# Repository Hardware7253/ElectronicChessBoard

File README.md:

# Electronic Chess Board
Welcome to the Electronic Chess Board project repository. This project combines an electronic chess board with a chess engine, offering a more tactile way to train against an AI opponent.

## Overview
The project's core objective is to deliver an interactive chess experience, allowing users to engage in matches against an AI opponent.
This AI opponent employs a minimax algorithm for strategic decision-making, with a variable search depth of 3 to 6 based on time availability. 
The chess board integrates 64 hall effect sensors to precisely detect piece positions, while the AI's moves are visually indicated using 64 LEDs.

## Code
In the [Code](/Code) directory, you'll find the firmware that powers the project. This firmware includes the chess engine responsible for AI decision-making.
The project is programmed in embedded rust, and is designed to run on the custom STM32F103C8T6 chess board.

## CAD
The [CAD](/Cad) directory contains KiCad schematics for the custom chess board PCB. Additionally, you'll find laser cutting files and 3D design files for the casing of the electronic chess board.
Manufacturing outputs for the PCB can be found in the [Manufacture](/Cad/ChessBoardKiCad/Manufacture) directory.

# Manual

## Starting the game
To begin playing, the game board will prompt you to select your team—black or white. Simply press the button while your desired team is displayed on the screen.

## Setting up the board
After starting the game, you'll be prompted to set up the chessboard. Arrange the 32 chess pieces in their starting positions, with the color that represents your team closest to you. For instance, if you are playing as the black team, ensure that the black pieces are positioned on the bottom of the board closest to you. If you need assistance during this process, you can hold down the button at any time. Doing so will illuminate LEDs on the board, indicating missing pieces or incorrectly placed ones. Once all pieces are correctly positioned, the game will automatically commence.

## Playing the game
The game follows a turn-based structure with both the user and the chess engine taking their respective turns. To make a move, simply move a chess piece and press the button to confirm that you have completed your turn. When it's the computer's turn to move, it will signal its move by blinking LEDs to indicate the destination square.

## Capturing
When capturing an opponent's piece, start by removing the captured piece from the board. Then, move your piece to its final destination and press the button to signal the end of your turn. This behavior is consistent with en passant moves, where you must first remove the captured pawn from the board before completing your move.

## Castling
To execute a castling move, move your king to its castled position without moving the rook. Press the button to indicate that you have finished your turn. After this, you may move your rook to the opposite side of the king to complete the castling maneuver.

## Errors
Errors are most likely to occur when an illegal move is made. The board's LEDs will illuminate to highlight the pieces that need adjustment to rectify the error. Additionally, the LCD screen will prompt you to revert the piece positions.

Errors may also happen when pieces are moved during the chess engine's turn. In such cases, you may notice multiple LEDs being lit up, some indicating the engine's move and others indicating pieces in the wrong position. This typically occurs when one or more pieces are slightly off-center on their squares. To resolve this issue, simply adjust the misaligned pieces inward slightly to correct the error.

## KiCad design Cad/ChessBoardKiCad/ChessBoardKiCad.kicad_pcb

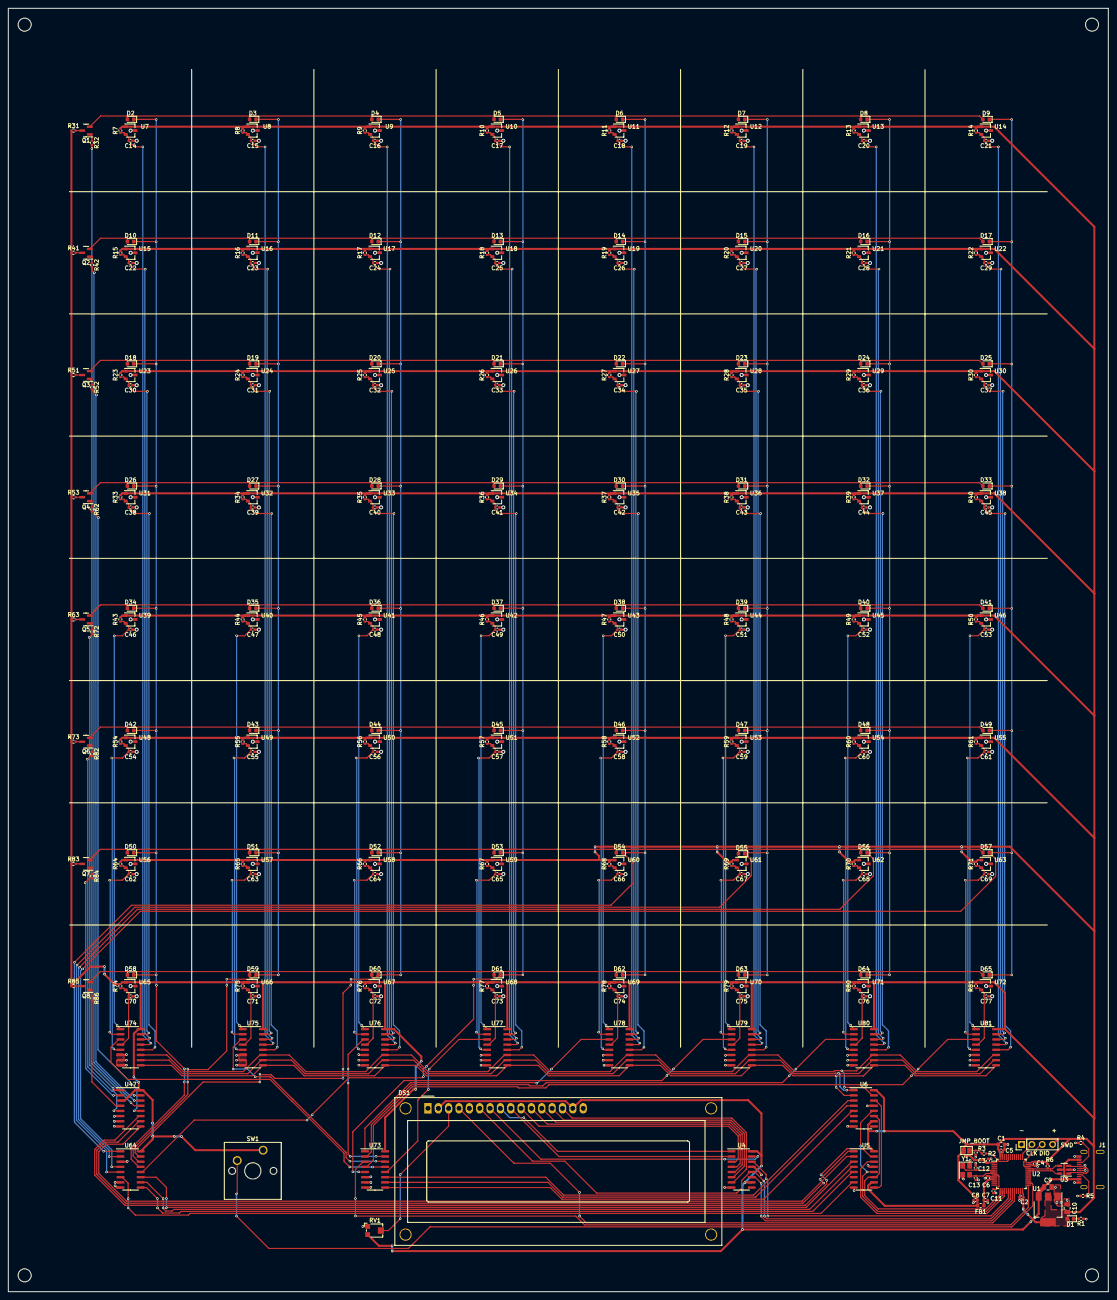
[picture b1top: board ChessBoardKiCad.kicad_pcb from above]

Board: 2 copper layers, 270.0 x 315.0 mm, 329 parts (0 on the bottom side), 162 nets.

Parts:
C1: 10u; C_0603_1608Metric
C2, C3, C4, C5, C11, C14, C15, C16, C17, C18, C19, C20, C21, C22, C23, C24, C25, C26, C27, C28, C29, C30, C31, C32, C33, C34, C35, C36, C37, C38, C39, C40, C41, C42, C43, C44, C45, C46, C47, C48, C49, C50, C51, C52, C53, C54, C55, C56, C57, C58, C59, C60, C61, C62, C63, C64, C65, C66, C67, C68, C69, C70, C71, C72, C73, C74, C75, C76, C77: 100n; C_0402_1005Metric
C6: 10n; C_0402_1005Metric
C7, C8: 1u; C_0402_1005Metric
C9, C10: 22u; C_0805_2012Metric
C12, C13: 14p; C_0402_1005Metric
D1, D2, D3, D4, D5, D6, D7, D8, D9, D10, D11, D12, D13, D14, D15, D16, D17, D18, D19, D20, D21, D22, D23, D24, D25, D26, D27, D28, D29, D30, D31, D32, D33, D34, D35, D36, D37, D38, D39, D40, D41, D42, D43, D44, D45, D46, D47, D48, D49, D50, D51, D52, D53, D54, D55, D56, D57, D58, D59, D60, D61, D62, D63, D64, D65: RED; LED_0603_1608Metric
DS1: WC1602A
FB1: 120R; L_0603_1608Metric
H1, H2, H3, H4: MountingHole; MountingHole_3.2mm_M3
J1: USB_C_Receptacle; USB-310D-B-SU
J2: Conn_01x04_Pin; PinHeader_1x04_P2.54mm_Vertical
JP1: SolderJumper_2_Open; SolderJumper-2_P1.3mm_Open_Pad1.0x1.5mm
Q1, Q2, Q3, Q4, Q5, Q6, Q7, Q8: S9013; SOT-23
R1, R6, R31, R41, R51, R53, R63, R73, R83, R85: 1k5; R_0402_1005Metric
R2, R3, R32, R42, R52, R62, R72, R82, R84, R86: 10k; R_0402_1005Metric
R4, R5: 5k1; R_0402_1005Metric
R7, R8, R9, R10, R11, R12, R13, R14, R15, R16, R17, R18, R19, R20, R21, R22, R23, R24, R25, R26, R27, R28, R29, R30, R33, R34, R35, R36, R37, R38, R39, R40, R43, R44, R45, R46, R47, R48, R49, R50, R54, R55, R56, R57, R58, R59, R60, R61, R64, R65, R66, R67, R68, R69, R70, R71, R74, R75, R76, R77, R78, R79, R80, R81: 2k7; R_0402_1005Metric
RV1: 10k; Potentiometer_Bourns_TC33X_Vertical
SW1: SW_SPST; SW_Cherry_MX_1.00u_PCB
U1: AMS1117-3.3; SOT-223-3_TabPin2
U2: STM32F103C8T6; LQFP-48_7x7mm_P0.5mm
U3: USBLC6-2SC6; SOT-23-6
U4, U5, U6: 74HC595; SOIC-16_3.9x9.9mm_P1.27mm
U7, U8, U9, U10, U11, U12, U13, U14, U15, U16, U17, U18, U19, U20, U21, U22, U23, U24, U25, U26, U27, U28, U29, U30, U31, U32, U33, U34, U35, U36, U37, U38, U39, U40, U41, U42, U43, U44, U45, U46, U48, U49, U50, U51, U52, U53, U54, U55, U56, U57, U58, U59, U60, U61, U62, U63, U65, U66, U67, U68, U69, U70, U71, U72: UHE4913G-AE3-R; SOT-23W
U47, U64, U73, U74, U75, U76, U77, U78, U79, U80, U81: CD4051BM; SOIC-16_3.9x9.9mm_P1.27mm
Y1: 8Mhz; Crystal_SMD_3225-4Pin_3.2x2.5mm

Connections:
+3.3V: C1.1, C2.1, C3.1, C4.1, C5.1, C8.1, C10.1, D1.2 (A), FB1.2, J2.4, JP1.1 (A), R6.2, R7.1, R8.1, R9.1, R10.1, R11.1, R12.1, R13.1, R14.1, R15.1, R16.1, R17.1, R18.1, R19.1, R20.1, R21.1, R22.1, R23.1, R24.1, R25.1, R26.1, R27.1, R28.1, R29.1, R30.1, R31.1, R33.1, R34.1, R35.1, R36.1, R37.1, R38.1, R39.1, R40.1, R41.1, R43.1, R44.1, R45.1, R46.1, R47.1, R48.1, R49.1, R50.1, R51.1, R53.1, R54.1, R55.1, R56.1, R57.1, R58.1, R59.1, R60.1, R61.1, R63.1, R64.1, R65.1, R66.1, R67.1, R68.1, R69.1, R70.1, R71.1, R73.1, R74.1, R75.1, R76.1, R77.1, R78.1, R79.1, R80.1, R81.1, R83.1, R85.1, SW1.1 (A), U1.2 (VO), U2.1 (VBAT), U2.24 (VDD), U2.36 (VDD), U2.48 (VDD), U5.10 (~SRCLR), U5.16 (VCC), U6.10 (~SRCLR), U6.16 (VCC), U7.1 (VCC), U8.1 (VCC), U9.1 (VCC), U10.1 (VCC), U11.1 (VCC), U12.1 (VCC), U13.1 (VCC), U14.1 (VCC), U15.1 (VCC), U16.1 (VCC), U17.1 (VCC), U18.1 (VCC), U19.1 (VCC), U20.1 (VCC), U21.1 (VCC), U22.1 (VCC), U23.1 (VCC), U24.1 (VCC), U25.1 (VCC), U26.1 (VCC), U27.1 (VCC), U28.1 (VCC), U29.1 (VCC), U30.1 (VCC), U31.1 (VCC), U32.1 (VCC), U33.1 (VCC), U34.1 (VCC), U35.1 (VCC), U36.1 (VCC), U37.1 (VCC), U38.1 (VCC), U39.1 (VCC), U40.1 (VCC), U41.1 (VCC), U42.1 (VCC), U43.1 (VCC), U44.1 (VCC), U45.1 (VCC), U46.1 (VCC), U47.3 (X), U47.16 (VDD), U48.1 (VCC), U49.1 (VCC), U50.1 (VCC), U51.1 (VCC), U52.1 (VCC), U53.1 (VCC), U54.1 (VCC), U55.1 (VCC), U56.1 (VCC), U57.1 (VCC), U58.1 (VCC), U59.1 (VCC), U60.1 (VCC), U61.1 (VCC), U62.1 (VCC), U63.1 (VCC), U64.16 (VDD), U65.1 (VCC), U66.1 (VCC), U67.1 (VCC), U68.1 (VCC), U69.1 (VCC), U70.1 (VCC), U71.1 (VCC), U72.1 (VCC), U73.16 (VDD), U74.16 (VDD), U75.16 (VDD), U76.16 (VDD), U77.16 (VDD), U78.16 (VDD), U79.16 (VDD), U80.16 (VDD), U81.16 (VDD)
+3.3VA: C6.1, C7.1, FB1.1, U2.9 (VDDA)
/BOOT0: R2.1, U2.44 (BOOT0)
/CONT_1: DS1.3 (VO), RV1.2
/GRID_REGS_SER_LINK: U5.9 (QH'), U6.14 (SER)
/HSE_IN: C12.1, U2.5 (PD0), Y1.1
/HSE_OUT: C13.1, U2.6 (PD1), Y1.3
/JMP_BOOT0: JP1.2 (B), R2.2, R3.2
/LCD1_D0: DS1.7 (D0), U4.15 (QA)
/LCD1_D1: DS1.8 (D1), U4.1 (QB)
/LCD1_D2: DS1.9 (D2), U4.2 (QC)
/LCD1_D3: DS1.10 (D3), U4.3 (QD)
/LCD1_D4: DS1.11 (D4), U4.4 (QE)
/LCD1_D5: DS1.12 (D5), U4.5 (QF)
/LCD1_D6: DS1.13 (D6), U4.6 (QG)
/LCD1_D7: DS1.14 (D7), U4.7 (QH)
/NRST: C11.1, U2.7 (NRST)
/PWR_LED_K: D1.1 (K), R1.2
/R0TB: Q1.1 (B), R32.1
/R0TC: Q1.3 (C), R31.2
/R0TE: D2.2 (A), D3.2 (A), D4.2 (A), D5.2 (A), D6.2 (A), D7.2 (A), D8.2 (A), D9.2 (A), Q1.2 (E)
/R1TB: Q2.1 (B), R42.1
/R1TC: Q2.3 (C), R41.2
/R1TE: D10.2 (A), D11.2 (A), D12.2 (A), D13.2 (A), D14.2 (A), D15.2 (A), D16.2 (A), D17.2 (A), Q2.2 (E)
/R2TB: Q3.1 (B), R52.1
/R2TC: Q3.3 (C), R51.2
/R2TE: D18.2 (A), D19.2 (A), D20.2 (A), D21.2 (A), D22.2 (A), D23.2 (A), D24.2 (A), D25.2 (A), Q3.2 (E)
/R3TB: Q4.1 (B), R62.1
/R3TC: Q4.3 (C), R53.2
/R3TE: D26.2 (A), D27.2 (A), D28.2 (A), D29.2 (A), D30.2 (A), D31.2 (A), D32.2 (A), D33.2 (A), Q4.2 (E)
/R4TB: Q5.1 (B), R72.1
/R4TC: Q5.3 (C), R63.2
/R4TE: D34.2 (A), D35.2 (A), D36.2 (A), D37.2 (A), D38.2 (A), D39.2 (A), D40.2 (A), D41.2 (A), Q5.2 (E)
/R5TB: Q6.1 (B), R82.1
/R5TC: Q6.3 (C), R73.2
/R5TE: D42.2 (A), D43.2 (A), D44.2 (A), D45.2 (A), D46.2 (A), D47.2 (A), D48.2 (A), D49.2 (A), Q6.2 (E)
/R6TB: Q7.1 (B), R84.1
/R6TC: Q7.3 (C), R83.2
/R6TE: D50.2 (A), D51.2 (A), D52.2 (A), D53.2 (A), D54.2 (A), D55.2 (A), D56.2 (A), D57.2 (A), Q7.2 (E)
/R7TB: Q8.1 (B), R86.1
/R7TC: Q8.3 (C), R85.2
/R7TE: D58.2 (A), D59.2 (A), D60.2 (A), D61.2 (A), D62.2 (A), D63.2 (A), D64.2 (A), D65.2 (A), Q8.2 (E)
/SWCLK: J2.2, U2.37 (PA14)
/SWDIO: J2.3, U2.34 (PA13)
/USB_CC1: J1.A5 (CC1), R5.2
/USB_CC2: J1.B5 (CC2), R4.2
BUTTON: SW1.2 (B), U2.26 (PB13)
DISABLE_LEDS: U5.7 (QH), U64.6 (Inh)
GND: C1.2, C2.2, C3.2, C4.2, C5.2, C6.2, C7.2, C8.2, C9.2, C10.2, C11.2, C12.2, C13.2, C14.2, C15.2, C16.2, C17.2, C18.2, C19.2, C20.2, C21.2, C22.2, C23.2, C24.2, C25.2, C26.2, C27.2, C28.2, C29.2, C30.2, C31.2, C32.2, C33.2, C34.2, C35.2, C36.2, C37.2, C38.2, C39.2, C40.2, C41.2, C42.2, C43.2, C44.2, C45.2, C46.2, C47.2, C48.2, C49.2, C50.2, C51.2, C52.2, C53.2, C54.2, C55.2, C56.2, C57.2, C58.2, C59.2, C60.2, C61.2, C62.2, C63.2, C64.2, C65.2, C66.2, C67.2, C68.2, C69.2, C70.2, C71.2, C72.2, C73.2, C74.2, C75.2, C76.2, C77.2, DS1.1 (VSS), DS1.5 (R/W), DS1.16 (LED(-)), J1.A1 (GND), J1.A12 (GND), J1.B1 (GND), J1.B12 (GND), J2.1, R1.1, R3.1, R4.1, R5.1, RV1.1, U1.1 (GND), U2.8 (VSSA), U2.23 (VSS), U2.35 (VSS), U2.47 (VSS), U3.2 (GND), U4.8 (GND), U4.13 (~OE), U5.8 (GND), U5.13 (~OE), U6.8 (GND), U6.13 (~OE), U7.3 (GND), U8.3 (GND), U9.3 (GND), U10.3 (GND), U11.3 (GND), U12.3 (GND), U13.3 (GND), U14.3 (GND), U15.3 (GND), U16.3 (GND), U17.3 (GND), U18.3 (GND), U19.3 (GND), U20.3 (GND), U21.3 (GND), U22.3 (GND), U23.3 (GND), U24.3 (GND), U25.3 (GND), U26.3 (GND), U27.3 (GND), U28.3 (GND), U29.3 (GND), U30.3 (GND), U31.3 (GND), U32.3 (GND), U33.3 (GND), U34.3 (GND), U35.3 (GND), U36.3 (GND), U37.3 (GND), U38.3 (GND), U39.3 (GND), U40.3 (GND), U41.3 (GND), U42.3 (GND), U43.3 (GND), U44.3 (GND), U45.3 (GND), U46.3 (GND), U47.6 (Inh), U47.7 (VEE), U47.8 (VSS), U48.3 (GND), U49.3 (GND), U50.3 (GND), U51.3 (GND), U52.3 (GND), U53.3 (GND), U54.3 (GND), U55.3 (GND), U56.3 (GND), U57.3 (GND), U58.3 (GND), U59.3 (GND), U60.3 (GND), U61.3 (GND), U62.3 (GND), U63.3 (GND), U64.3 (X), U64.7 (VEE), U64.8 (VSS), U65.3 (GND), U66.3 (GND), U67.3 (GND), U68.3 (GND), U69.3 (GND), U70.3 (GND), U71.3 (GND), U72.3 (GND), U73.6 (Inh), U73.7 (VEE), U73.8 (VSS), U74.6 (Inh), U74.7 (VEE), U74.8 (VSS), U75.6 (Inh), U75.7 (VEE), U75.8 (VSS), U76.6 (Inh), U76.7 (VEE), U76.8 (VSS), U77.6 (Inh), U77.7 (VEE), U77.8 (VSS), U78.6 (Inh), U78.7 (VEE), U78.8 (VSS), U79.6 (Inh), U79.7 (VEE), U79.8 (VSS), U80.6 (Inh), U80.7 (VEE), U80.8 (VSS), U81.6 (Inh), U81.7 (VEE), U81.8 (VSS), Y1.2, Y1.4
GRID_LATCH: U2.14 (PA4), U5.12 (RCLK), U6.12 (RCLK)
GRID_SER_CLK: U2.13 (PA3), U5.11 (SRCLK), U6.11 (SRCLK)
GRID_SER_DATA: U2.15 (PA5), U5.14 (SER)
HALL_C0: U73.13 (X0), U74.3 (X)
HALL_C0R0: C14.1, R7.2, U7.2 (VOUT), U74.13 (X0)
HALL_C0R1: C22.1, R15.2, U15.2 (VOUT), U74.14 (X1)
HALL_C0R2: C30.1, R23.2, U23.2 (VOUT), U74.15 (X2)
HALL_C0R3: C38.1, R33.2, U31.2 (VOUT), U74.12 (X3)
HALL_C0R4: C46.1, R43.2, U39.2 (VOUT), U74.1 (X4)
HALL_C0R5: C54.1, R54.2, U48.2 (VOUT), U74.5 (X5)
HALL_C0R6: C62.1, R64.2, U56.2 (VOUT), U74.2 (X6)
HALL_C0R7: C70.1, R74.2, U65.2 (VOUT), U74.4 (X7)
HALL_C1: U73.14 (X1), U75.3 (X)
HALL_C1R0: C15.1, R8.2, U8.2 (VOUT), U75.13 (X0)
HALL_C1R1: C23.1, R16.2, U16.2 (VOUT), U75.14 (X1)
HALL_C1R2: C31.1, R24.2, U24.2 (VOUT), U75.15 (X2)
HALL_C1R3: C39.1, R34.2, U32.2 (VOUT), U75.12 (X3)
HALL_C1R4: C47.1, R44.2, U40.2 (VOUT), U75.1 (X4)
HALL_C1R5: C55.1, R55.2, U49.2 (VOUT), U75.5 (X5)
HALL_C1R6: C63.1, R65.2, U57.2 (VOUT), U75.2 (X6)
HALL_C1R7: C71.1, R75.2, U66.2 (VOUT), U75.4 (X7)
HALL_C2: U73.15 (X2), U76.3 (X)
HALL_C2R0: C16.1, R9.2, U9.2 (VOUT), U76.13 (X0)
HALL_C2R1: C24.1, R17.2, U17.2 (VOUT), U76.14 (X1)
HALL_C2R2: C32.1, R25.2, U25.2 (VOUT), U76.15 (X2)
HALL_C2R3: C40.1, R35.2, U33.2 (VOUT), U76.12 (X3)
HALL_C2R4: C48.1, R45.2, U41.2 (VOUT), U76.1 (X4)
HALL_C2R5: C56.1, R56.2, U50.2 (VOUT), U76.5 (X5)
HALL_C2R6: C64.1, R66.2, U58.2 (VOUT), U76.2 (X6)
HALL_C2R7: C72.1, R76.2, U67.2 (VOUT), U76.4 (X7)
HALL_C3: U73.12 (X3), U77.3 (X)
HALL_C3R0: C17.1, R10.2, U10.2 (VOUT), U77.13 (X0)
HALL_C3R1: C25.1, R18.2, U18.2 (VOUT), U77.14 (X1)
HALL_C3R2: C33.1, R26.2, U26.2 (VOUT), U77.15 (X2)
HALL_C3R3: C41.1, R36.2, U34.2 (VOUT), U77.12 (X3)
HALL_C3R4: C49.1, R46.2, U42.2 (VOUT), U77.1 (X4)
HALL_C3R5: C57.1, R57.2, U51.2 (VOUT), U77.5 (X5)
HALL_C3R6: C65.1, R67.2, U59.2 (VOUT), U77.2 (X6)
HALL_C3R7: C73.1, R77.2, U68.2 (VOUT), U77.4 (X7)
HALL_C4: U73.1 (X4), U78.3 (X)
HALL_C4R0: C18.1, R11.2, U11.2 (VOUT), U78.13 (X0)
HALL_C4R1: C26.1, R19.2, U19.2 (VOUT), U78.14 (X1)
HALL_C4R2: C34.1, R27.2, U27.2 (VOUT), U78.15 (X2)
HALL_C4R3: C42.1, R37.2, U35.2 (VOUT), U78.12 (X3)
HALL_C4R4: C50.1, R47.2, U43.2 (VOUT), U78.1 (X4)
HALL_C4R5: C58.1, R58.2, U52.2 (VOUT), U78.5 (X5)
HALL_C4R6: C66.1, R68.2, U60.2 (VOUT), U78.2 (X6)
HALL_C4R7: C74.1, R78.2, U69.2 (VOUT), U78.4 (X7)
HALL_C5: U73.5 (X5), U79.3 (X)
HALL_C5R0: C19.1, R12.2, U12.2 (VOUT), U79.13 (X0)
HALL_C5R1: C27.1, R20.2, U20.2 (VOUT), U79.14 (X1)
HALL_C5R2: C35.1, R28.2, U28.2 (VOUT), U79.15 (X2)
HALL_C5R3: C43.1, R38.2, U36.2 (VOUT), U79.12 (X3)
HALL_C5R4: C51.1, R48.2, U44.2 (VOUT), U79.1 (X4)
HALL_C5R5: C59.1, R59.2, U53.2 (VOUT), U79.5 (X5)
HALL_C5R6: C67.1, R69.2, U61.2 (VOUT), U79.2 (X6)
HALL_C5R7: C75.1, R79.2, U70.2 (VOUT), U79.4 (X7)
HALL_C6: U73.2 (X6), U80.3 (X)
HALL_C6R0: C20.1, R13.2, U13.2 (VOUT), U80.13 (X0)
HALL_C6R1: C28.1, R21.2, U21.2 (VOUT), U80.14 (X1)
HALL_C6R2: C36.1, R29.2, U29.2 (VOUT), U80.15 (X2)
HALL_C6R3: C44.1, R39.2, U37.2 (VOUT), U80.12 (X3)
HALL_C6R4: C52.1, R49.2, U45.2 (VOUT), U80.1 (X4)
HALL_C6R5: C60.1, R60.2, U54.2 (VOUT), U80.5 (X5)
HALL_C6R6: C68.1, R70.2, U62.2 (VOUT), U80.2 (X6)
HALL_C6R7: C76.1, R80.2, U71.2 (VOUT), U80.4 (X7)
HALL_C7: U73.4 (X7), U81.3 (X)
HALL_C7R0: C21.1, R14.2, U14.2 (VOUT), U81.13 (X0)
HALL_C7R1: C29.1, R22.2, U22.2 (VOUT), U81.14 (X1)
HALL_C7R2: C37.1, R30.2, U30.2 (VOUT), U81.15 (X2)
HALL_C7R3: C45.1, R40.2, U38.2 (VOUT), U81.12 (X3)
HALL_C7R4: C53.1, R50.2, U46.2 (VOUT), U81.1 (X4)
HALL_C7R5: C61.1, R61.2, U55.2 (VOUT), U81.5 (X5)
HALL_C7R6: C69.1, R71.2, U63.2 (VOUT), U81.2 (X6)
HALL_C7R7: C77.1, R81.2, U72.2 (VOUT), U81.4 (X7)
HALL_COL_A: U6.3 (QD), U73.11 (A)
HALL_COL_B: U6.4 (QE), U73.10 (B)
HALL_COL_C: U6.5 (QF), U73.9 (C)
HALL_ROW_A: U6.15 (QA), U74.11 (A), U75.11 (A), U76.11 (A), U77.11 (A), U78.11 (A), U79.11 (A), U80.11 (A), U81.11 (A)
HALL_ROW_B: U6.1 (QB), U74.10 (B), U75.10 (B), U76.10 (B), U77.10 (B), U78.10 (B), U79.10 (B), U80.10 (B), U81.10 (B)
HALL_ROW_C: U6.2 (QC), U74.9 (C), U75.9 (C), U76.9 (C), U77.9 (C), U78.9 (C), U79.9 (C), U80.9 (C), U81.9 (C)
LCD_LATCH: DS1.6 (E), U2.18 (PB0), U4.12 (RCLK)
LCD_RS: DS1.4 (RS), U2.20 (PB2)
LCD_SER_CLK: U2.19 (PB1), U4.11 (SRCLK)
LCD_SER_DATA: U2.17 (PA7), U4.14 (SER)
LED_C0: D2.1 (K), D10.1 (K), D18.1 (K), D26.1 (K), D34.1 (K), D42.1 (K), D50.1 (K), D58.1 (K), U64.13 (X0)
LED_C1: D3.1 (K), D11.1 (K), D19.1 (K), D27.1 (K), D35.1 (K), D43.1 (K), D51.1 (K), D59.1 (K), U64.14 (X1)
LED_C2: D4.1 (K), D12.1 (K), D20.1 (K), D28.1 (K), D36.1 (K), D44.1 (K), D52.1 (K), D60.1 (K), U64.15 (X2)
LED_C3: D5.1 (K), D13.1 (K), D21.1 (K), D29.1 (K), D37.1 (K), D45.1 (K), D53.1 (K), D61.1 (K), U64.12 (X3)
LED_C4: D6.1 (K), D14.1 (K), D22.1 (K), D30.1 (K), D38.1 (K), D46.1 (K), D54.1 (K), D62.1 (K), U64.1 (X4)
LED_C5: D7.1 (K), D15.1 (K), D23.1 (K), D31.1 (K), D39.1 (K), D47.1 (K), D55.1 (K), D63.1 (K), U64.5 (X5)
LED_C6: D8.1 (K), D16.1 (K), D24.1 (K), D32.1 (K), D40.1 (K), D48.1 (K), D56.1 (K), D64.1 (K), U64.2 (X6)
LED_C7: D9.1 (K), D17.1 (K), D25.1 (K), D33.1 (K), D41.1 (K), D49.1 (K), D57.1 (K), D65.1 (K), U64.4 (X7)
LED_COL_A: U5.3 (QD), U64.11 (A)
LED_COL_B: U5.4 (QE), U64.10 (B)
LED_COL_C: U5.5 (QF), U64.9 (C)
LED_R0: R32.2, U47.13 (X0)
LED_R1: R42.2, U47.14 (X1)
LED_R2: R52.2, U47.15 (X2)
LED_R3: R62.2, U47.12 (X3)
LED_R4: R72.2, U47.1 (X4)
LED_R5: R82.2, U47.5 (X5)
LED_R6: R84.2, U47.2 (X6)
LED_R7: R86.2, U47.4 (X7)
LED_ROW_A: U5.15 (QA), U47.11 (A)
LED_ROW_B: U5.1 (QB), U47.10 (B)
LED_ROW_C: U5.2 (QC), U47.9 (C)
SELECTED_HALL: U2.25 (PB12), U73.3 (X)
USB_CON_D+: J1.A6 (D+), J1.B6 (D+), U3.3 (I/O2)
USB_CON_D-: J1.A7 (D-), J1.B7 (D-), U3.1 (I/O1)
USB_D+: R6.1, U2.33 (PA12), U3.4 (I/O2)
USB_D-: U2.32 (PA11), U3.6 (I/O1)
VBUS: C9.1, DS1.2 (VDD), DS1.15 (LED(+)), J1.A4 (VBUS), J1.A9 (VBUS), J1.B4 (VBUS), J1.B9 (VBUS), RV1.3, U1.3 (VI), U3.5 (VBUS), U4.10 (~SRCLR), U4.16 (VCC)

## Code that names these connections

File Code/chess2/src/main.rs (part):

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
    // Initialise hall and led grid shift register
    let mut grid_sr = embedded::ShiftRegister {
        clock: gpioa.pa3.into_push_pull_output(&mut gpioa.crl).downgrade(),
        data: gpioa.pa5.into_push_pull_output(&mut gpioa.crl).downgrade(),
        latch: gpioa.pa4.into_push_pull_output(&mut gpioa.crl).downgrade(),
        bits: 16,
    };
    grid_sr.init(&mut delay);
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    // Initialise character lcd
    let mut lcd = embedded::character_lcd::Lcd {
        shift_register: embedded::ShiftRegister {
            clock: gpiob.pb1.into_push_pull_output(&mut gpiob.crl).downgrade(),
            data: gpioa.pa7.into_push_pull_output(&mut gpioa.crl).downgrade(),
            latch: gpiob.pb0.into_push_pull_output(&mut gpiob.crl).downgrade(),
            bits: 8,
        },
        register_select: gpiob.pb2.into_push_pull_output(&mut gpiob.crl).downgrade(),
    };
    lcd.init(&mut delay);

    let hall_sensor = gpiob.pb12.into_floating_input(&mut gpiob.crh).downgrade(); // Pin to read value of the selected hall sensor

    let mut button = embedded::button::Button {
        pin: gpiob.pb13.into_pull_down_input(&mut gpiob.crh).downgrade(),
        press_raw: false,
        press_start_cycle: None,
        long_press_cycles: embedded::ms_to_cycles(650, clock_mhz as u64), // Button needs to be held for atleast 650ms for a long press
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
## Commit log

2023-03-17 Full utilization of fen
2023-03-17 Started move generation
    Added function to check if a move on a bitboard still fits within
    cartesian bitboard. Also removed constants for piece_ids.
2023-03-18 Added basic move generation
    Made a function which returns a bitboard, where a bit switched to 1
    indicates that the given piece can move there. No advanced functionality
    such as en passant, double move, or castling is implemented yet.
2023-03-19 Added special pawn moves
    Added en passant, double moves, and special capture moves.
2023-03-21 Added a castling function
2023-03-22 Bugfixed castle function
2023-03-24 Added function to generate enemy attacks
    Function generates enemy attacks, and stores coordinates of pieces
    putting the king in check.
2023-03-25 Added function to check for mate
    Returns true/false if a king is in mate. Can be used to check for
    checkmate and stalemate.
2023-03-26 is_mate bufix
    Fixed scenario where a checkmate was not registered because a pawn had a
    valid move.
2023-03-29 Added new_turn function
    Function returns a new board if the move is valid including updated bitboards, points, etc.
2023-03-30 new_turn now returns an error enum
    Error enum has more detailed information about why the move failed.
    Additionally added check to see if moving the piece results in checkmate
    or stalemate so the game can be ended.
2023-03-31 Added a move orderer
    To be used with best_move minimax function
2023-03-31 Added gen_best_move function
    Finds the best move on the board with a given depth. Uses minimax
    algorithms. Also made bugfixes regarding kings being able to move into
    check.
2023-03-31 Added alpha beta pruning
    Branches will now be pruned if they aren't necassary to search. Fixed
    bug in is_mate. Fixed bug in new_turn where en_passant capture would not
    give any value.
2023-03-31 More is_mate bugfixes
    Fixed is_mate not accounting for moves which can block the checking
    pieces path.
2023-04-04 Added fen_encode function
    Made a debugging function to encode the engines board representation into a fen
    string.
2023-04-05 midway through is_mate bugfix
2023-04-06 is_mate bugfix
    Fixed is_mate not accounting for moves of pieces not putting the king in
    check. This could be a problem if a friendly piece tries to capture an
    enemy piece putting the king in check, but exposes check from another
    piece.
2023-04-08 Game is playable against ai.
    Running the program now allows a player to verse the minimax algorithm.
    Bugfixed black pawns moving improperly aswell.
2023-04-09 Added pawn piece promotion
    Basic pawn promotion where they always promote to queens. Additionally
    made bugfix to castle where a king could still castle after it had moved.
    Also fixed moves bitboard not being correct for the king bits when queen and kingside could be
    castled to.
2023-04-13 Fixed bug in new_turn
    Fixed bug where team bitboards were not being updated when a capture
    happened. This caused false checkmates during a game.
2023-04-14 Bugfixed castle and is mate
    Removed unnecasary break from is mate to stop it returning early when
    checking if the king is able to move to any squares. Added condition to
    castle function that checks the rook at rook_bit actaully exists on the
    board.
2023-04-17 Overhauled is_mate function
    Rewrote the majority of is_mate to reduce bugs, and to simplify it.
    Simplifaction will allow easier bug fixing in the future.
2023-04-21 is_mate bugfix
    Fixed bug with is_mate where a square that a pawn was attacking could
    block a checking piece. The pawn couldn't actually move to this square,
    so a fix was implemented that checks if the pawn can actually move to
    the square where it is trying to block mate.
    Additionally tried to add heatmaps for piece advantageous squares. After
    implementing a new way to sort the moves in order_moves I tested it, and
2023-04-21 Opening heatmaps implemented
    The ai now conisders values from the opening heatmaps when making a
    move. Additionally fixed castling reseting turns_since_capture in
    new_turn.
2023-04-22 Added zobrist hashing
    Made relevant functions for zobrist hashing. They work but the feature
    hasn't yet been implemented into the best_move algorithm.
2023-04-24 Implemented transposition table
    Transpositions are now used in the best_move function to save time
    reevaluating positions. Additionally made the half move clock work
    properly.
2023-04-28 is_mate bugfix
    Added additional condition when returning false, king must not be in
    check after a move that blocks the initial check. Additionally made old
    moves in transposition table delete themselves. And gave a value for
    pawn promotion to queen. This encourages the algorithm to promote.
2023-05-01 Fixed typo affecting minimax algorithm
    Typo in the alpha beta pruning caused function to never return minimum
    values. The typo has been fixed. Additionally order_move now used a
    change in the heatmap value from the initial to the final square. So a
    piece is encouraged to hold an advantageous square.
2023-05-05 Added zobrist hashing to a test
    Speed of the best_move function can be more accurately tested
2023-05-07 Added iterative deepening
    Best moves from lower search depths are search first. This currently
    results in a longer search time overall. I think there is a bug in the
    pruning which I will have to fix.
2023-05-09 Changed alpha beta implementation
    Currently broken
2023-05-10 fixed alpha beta pruning
2023-05-12 Added timeout best_move function
    When the master branch of best_move has been running more than the
    maximum ammount of milliseconds it is aloud to run for it returns the pv
    move from a lower search depth.
2023-05-13 Removed vec and hashmaps
    Removed the transposition table which relies on hashmaps. And changed
    from a vec to an array for sorted moves at a detrement to performance.
    These changes were made to remove core functions reliance on std to make
    running on an embedded system easier.
2023-05-16 first embedded commit
    Removed unnecary debugging and testing code, and completely eliminated
    the std library. Project is now setup to run the chess engine on an
    stm32f103c8t6.
2023-05-28 Added KiCad project
    KiCad project contains the design and manufacturing outputs for the
    electronic chess board.
2023-05-30 file organisation
2023-06-01 Tweaked via placement
    Changed the position of two vias that were conflicting with the
    silkscreen. Re-generated gerbers
2023-06-07 Added hall sensor and led function
    Function allows an inddividual hall effect sensor or led on the board to
    be selected.
2023-06-14 Testing board peripherals
    Added an additional module for controlling the boards character lcd.
    Additionally tested reading from hall effect sensors, lighting leds, and
    printing to character lcd in main
2023-06-17 Added function to read halls
    Added new function to read the state of the physical board to a
    bitboard
2023-06-17 Added fusion file
    Added fusion 360 file for the chess board case
2023-06-21 Added counter and button modules
    Added modules to make interfacing with the internal counter and attached
    button easier.
2023-06-22 Changed variable naming
2023-06-22 Added team select
2023-06-30 Board initialisation and input
    The game will only start after the board has been setup properly by
    placing pieces in the right position. Also added a way to read a users
    move with error checking.
2023-07-03 Playable on hardware
    The game is now playable on the physical hardware. However, there is a
    game breaking bug where the board can't detect a capture move. Because
    it can't tell where the capturing piece moved.
2023-07-04 Fixed player capturing bug
    Fixed the bug where a player couldn't capture a piece because the
    find_bitboard_move function would return an error due to a piece being
    removed from the board. Now if a player first removes and enemy piece
    and then moves their piece there they can make a capture without error.
    However there is still a bug with the computer capturing.
2023-07-05 Fixed computer captures
    Now when a computer captures the player is expected to first remove
    their captured piece from the board, and then move the computer piece.
2023-07-14 Added qol features
    Added fifty move rule back into the game. Removed the effect of the
    opening heatmap after the early/mid game has ended. Added a menu to
    adjust the minimax maximum move time, and added a way to forfiet.
    Additionally added a benchmark for elapsed clock cycles calculating an
    opening move. Currently takes ~345913092 cycles.
2023-07-19 Fixed max search menu
    Fixed max search menu opening after the player made a turn
2023-07-21 Fixed bugs
    Fixed a bug where the cycle counter (struct version not DWT) would
    frequently reset due to a u32 value being used in a multiplication
    instead of a u64. This would cause the game to freeze because the time
    would reset while the minimax algorithm is running.
    Additionally fixed the computer telling you to castle a turn after it
    actually castled.
2023-07-22 Tidied code
    Removed most compilation warnings. Additionally made it so the player
    has to press the button to end the game after a stalemate or checkmate.
    This way the game won't end instantly and the player will have time to
    read the game over message.
2023-07-26 Bug fix
    Changes from last commit broke the is_mate function in some cases.
    Changed back to previous is_mate funciton to fix bugs, and refactored
    the appropriate section in is_mate to make it easier to understand.
    Fixed other misc bugs.
2023-07-29 Updated case design files
2023-08-17 Updated design files
    Improved screen cover design, and added an additional brace to the
    casing. Additionally added a manufacturing directory with dxf and stl
    files for the case.
2023-08-19 Added OpenSCAD models to design
    Added OpenSCAD models for spacers that are used for mounting the
    character lcd, and plate ontop of the PCB. These were initially intended
    to be washers, but 3D printing allows them to be one piece rather than
    multiple stacked washers. This makes assembly easier. Additionally added
    an OpenSCAD file for a chess base piece, which can be used to convert
    normal chess pieces into ones with magnets.
2023-09-13 Bugfix
    Fixed bug where game would brick if the player starts as the black team.
    Made additional usability improvements.
2023-09-20 Update README.md
    Started writing manual
2023-09-20 Update README.md
    Added complete manual
2025-05-08 Update README.md
    Add Picture
2026-03-19 Added a better image to readme
